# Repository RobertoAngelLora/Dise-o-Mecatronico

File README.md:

# Dise-o-Mecatronico
Materia Electiva de Mecatrónica - Diseño Mecatrónico

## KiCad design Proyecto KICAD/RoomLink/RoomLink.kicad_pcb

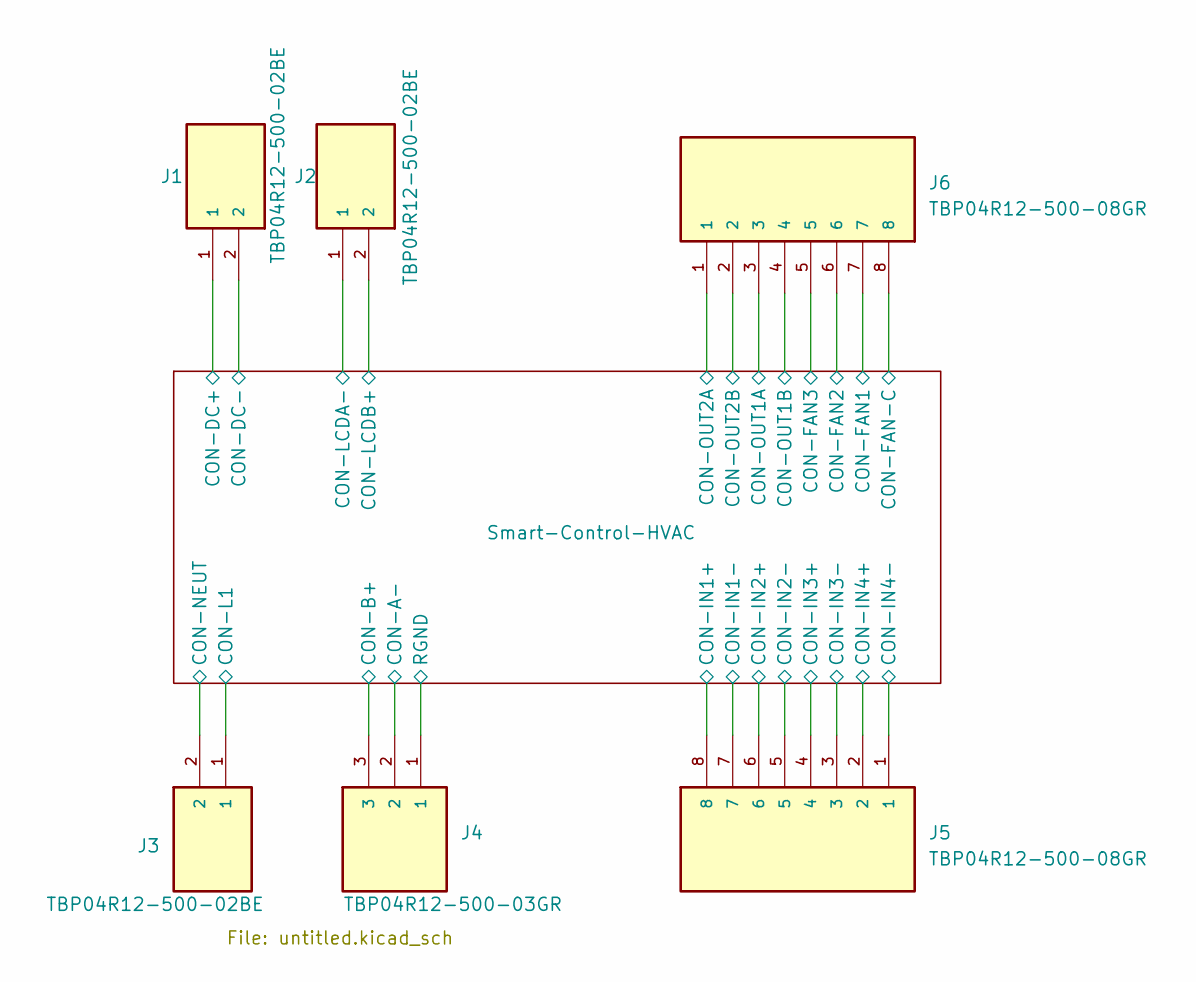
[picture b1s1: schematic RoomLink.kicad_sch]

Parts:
J1, J2, J3: TBP04R12-500-02BE; CUI_TBP04R12-500-02BE; PARTREV 1.0
J4: TBP04R12-500-03GR; CUI_TBP04R12-500-03GR; PARTREV 1.0
J5, J6: TBP04R12-500-08GR; CUI_TBP04R12-500-08GR; PARTREV 1.0

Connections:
/Smart-Control-HVAC/CON-A-: J4.2; also elsewhere on the board
/Smart-Control-HVAC/CON-B+: J4.3; also elsewhere on the board
/Smart-Control-HVAC/CON-DC+: J1.1; also elsewhere on the board
/Smart-Control-HVAC/CON-DC-: J1.2; also elsewhere on the board
/Smart-Control-HVAC/CON-FAN1: J6.7; also elsewhere on the board
/Smart-Control-HVAC/CON-FAN2: J6.6; also elsewhere on the board
/Smart-Control-HVAC/CON-FAN3: J6.5; also elsewhere on the board
/Smart-Control-HVAC/CON-FAN-C: J6.8; also elsewhere on the board
/Smart-Control-HVAC/CON-IN1+: J5.8; also elsewhere on the board
/Smart-Control-HVAC/CON-IN1-: J5.7; also elsewhere on the board
/Smart-Control-HVAC/CON-IN2+: J5.6; also elsewhere on the board
/Smart-Control-HVAC/CON-IN2-: J5.5; also elsewhere on the board
/Smart-Control-HVAC/CON-IN3+: J5.4; also elsewhere on the board
/Smart-Control-HVAC/CON-IN3-: J5.3; also elsewhere on the board
/Smart-Control-HVAC/CON-IN4+: J5.2; also elsewhere on the board
/Smart-Control-HVAC/CON-IN4-: J5.1; also elsewhere on the board
/Smart-Control-HVAC/CON-L1: J2.1; also elsewhere on the board
/Smart-Control-HVAC/CON-LCDA-: J3.1; also elsewhere on the board
/Smart-Control-HVAC/CON-LCDB+: J3.2; also elsewhere on the board
/Smart-Control-HVAC/CON-NEUT: J2.2; also elsewhere on the board
/Smart-Control-HVAC/CON-OUT1A: J6.3; also elsewhere on the board
/Smart-Control-HVAC/CON-OUT1B: J6.4; also elsewhere on the board
/Smart-Control-HVAC/CON-OUT2A: J6.1; also elsewhere on the board
/Smart-Control-HVAC/CON-OUT2B: J6.2; also elsewhere on the board
/Smart-Control-HVAC/RGND: J4.1; also elsewhere on the board

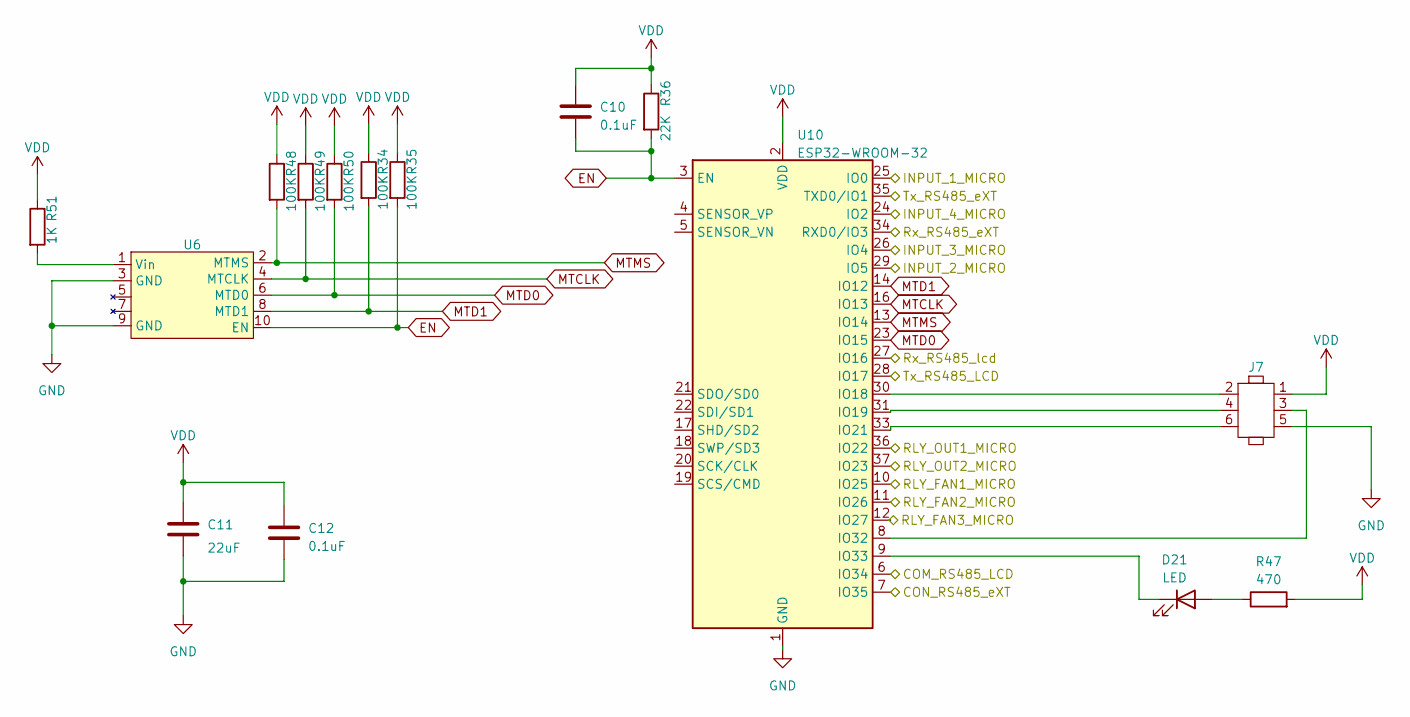
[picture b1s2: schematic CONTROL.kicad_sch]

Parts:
C10, C12: 0.1uF; C_0805_2012Metric
C11: 22uF; C_0805_2012Metric
D21: LED; D_0805_2012Metric
J7: PinHeader_2x03_P2.54mm_Vertical
R34, R35, R48, R49, R50: 100K; R_0805_2012Metric
R36: 22K; R_0805_2012Metric
R47: 470; R_0805_2012Metric
R51: 1K; R_0805_2012Metric
U6: PinHeader_2x05_P2.54mm_Vertical
U10: ESP32-WROOM-32

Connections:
/Smart-Control-HVAC/CONTROL/COM_RS485_LCD: U10.6 (IO34); also elsewhere on the board
/Smart-Control-HVAC/CONTROL/CON_RS485_eXT: U10.7 (IO35); also elsewhere on the board
/Smart-Control-HVAC/CONTROL/INPUT_1_MICRO: U10.25 (IO0); also elsewhere on the board
/Smart-Control-HVAC/CONTROL/INPUT_2_MICRO: U10.29 (IO5); also elsewhere on the board
/Smart-Control-HVAC/CONTROL/INPUT_3_MICRO: U10.26 (IO4); also elsewhere on the board
/Smart-Control-HVAC/CONTROL/INPUT_4_MICRO: U10.24 (IO2); also elsewhere on the board
/Smart-Control-HVAC/CONTROL/RLY_FAN1_MICRO: U10.10 (IO25); also elsewhere on the board
/Smart-Control-HVAC/CONTROL/RLY_FAN2_MICRO: U10.11 (IO26); also elsewhere on the board
/Smart-Control-HVAC/CONTROL/RLY_FAN3_MICRO: U10.12 (IO27); also elsewhere on the board
/Smart-Control-HVAC/CONTROL/RLY_OUT1_MICRO: U10.36 (IO22); also elsewhere on the board
/Smart-Control-HVAC/CONTROL/RLY_OUT2_MICRO: U10.37 (IO23); also elsewhere on the board
/Smart-Control-HVAC/CONTROL/Rx_RS485_eXT: U10.34 (RXD0/IO3); also elsewhere on the board
/Smart-Control-HVAC/CONTROL/Rx_RS485_lcd: U10.27 (IO16); also elsewhere on the board
/Smart-Control-HVAC/CONTROL/Tx_RS485_LCD: U10.28 (IO17); also elsewhere on the board
/Smart-Control-HVAC/CONTROL/Tx_RS485_eXT: U10.35 (TXD0/IO1); also elsewhere on the board
EN: C10.2, R35.2, R36.2, U6.10 (EN), U10.3 (EN)
GND: C11.2, C12.2, J7.5, U6.3 (GND), U6.9 (GND), U10.1 (GND), U10.15 (GND), U10.38 (GND), U10.39 (GND); also elsewhere on the board
MTCLK: R49.2, U6.4 (MTCLK), U10.16 (IO13)
MTD0: R50.2, U6.6 (MTD0), U10.23 (IO15)
MTD1: R34.2, U6.8 (MTD1), U10.14 (IO12)
MTMS: R48.2, U6.2 (MTMS), U10.13 (IO14)
unnamed: D21.2 (A), R47.1
unnamed: D21.1 (K), U10.9 (IO33)
unnamed: R51.2, U6.1 (Vin)
unnamed: J7.2, U10.30 (IO18)
unnamed: J7.4, U10.31 (IO19)
unnamed: J7.6, U10.33 (IO21)
unnamed: J7.3, U10.8 (IO32)
VDD: C10.1, C11.1, C12.1, J7.1, R34.1, R35.1, R36.1, R47.2, R48.1, R49.1, R50.1, R51.1, U10.2 (VDD); also elsewhere on the board

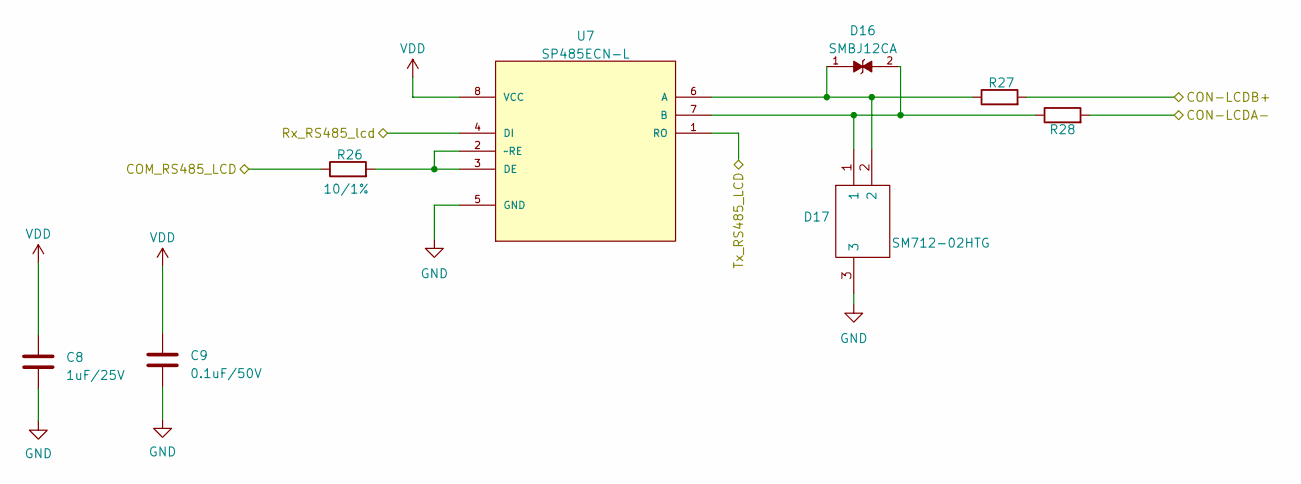
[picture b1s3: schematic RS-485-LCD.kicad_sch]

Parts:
C8: 1uF/25V; C_0805_2012Metric
C9: 0.1uF/50V; C_0805_2012Metric
D16: SMBJ12CA; DIOM4336X265N; PARTREV I2102
D17: SM712-02HTG; SM71202HTG; Mouser Part Number 576-SM712-02HTG
R26, R27, R28: 10/1%; R_0805_2012Metric
U7: SP485ECN-L; SOIC127P600X175-8N; MPN SP485ECN-L

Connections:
/Smart-Control-HVAC/CON-LCDA-: R28.2; also elsewhere on the board
/Smart-Control-HVAC/CON-LCDB+: R27.2; also elsewhere on the board
/Smart-Control-HVAC/CONTROL/COM_RS485_LCD: R26.1; also elsewhere on the board
/Smart-Control-HVAC/CONTROL/Rx_RS485_lcd: U7.4 (DI); also elsewhere on the board
/Smart-Control-HVAC/CONTROL/Tx_RS485_LCD: U7.1 (RO); also elsewhere on the board
GND: C8.2, C9.2, D17.3, U7.5 (GND); also elsewhere on the board
unnamed: D16.1, D17.2, R27.1, U7.6 (A)
unnamed: D16.2, D17.1, R28.1, U7.7 (B)
unnamed: R26.2, U7.2 (~RE), U7.3 (DE)
VDD: C8.1, C9.1, U7.8 (VCC); also elsewhere on the board

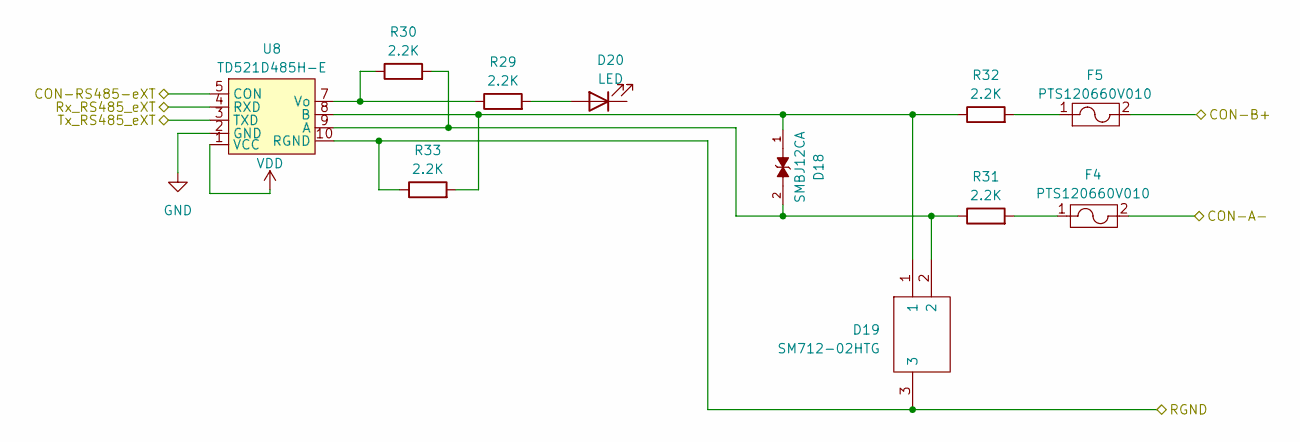
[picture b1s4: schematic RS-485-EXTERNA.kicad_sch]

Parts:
D18: SMBJ12CA; DIOM4336X265N; PARTREV I2102
D19: SM712-02HTG; SM71202HTG; Mouser Part Number 576-SM712-02HTG
D20: LED; LED_0805_2012Metric
F4, F5: PTS120660V010; RESC3115X65N
R29, R30, R31, R32, R33: 2.2K; R_0805_2012Metric
U8: TD521D485H-E

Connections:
/Smart-Control-HVAC/CON-A-: F4.2; also elsewhere on the board
/Smart-Control-HVAC/CON-B+: F5.2; also elsewhere on the board
/Smart-Control-HVAC/CONTROL/CON_RS485_eXT: U8.5 (CON); also elsewhere on the board
/Smart-Control-HVAC/CONTROL/Rx_RS485_eXT: U8.4 (RXD); also elsewhere on the board
/Smart-Control-HVAC/CONTROL/Tx_RS485_eXT: U8.3 (TXD); also elsewhere on the board
/Smart-Control-HVAC/RGND: D19.3, R33.1, U8.10 (RGND); also elsewhere on the board
GND: U8.2 (GND); also elsewhere on the board
unnamed: D20.2 (A), R29.2
unnamed: F4.1, R31.2
unnamed: F5.1, R32.2
unnamed: D18.2, D19.2, R30.2, R31.1, U8.9 (A)
unnamed: D18.1, D19.1, R32.1, R33.2, U8.8 (B)
unnamed: R29.1, R30.1, U8.7 (Vo)
VDD: U8.1 (VCC); also elsewhere on the board

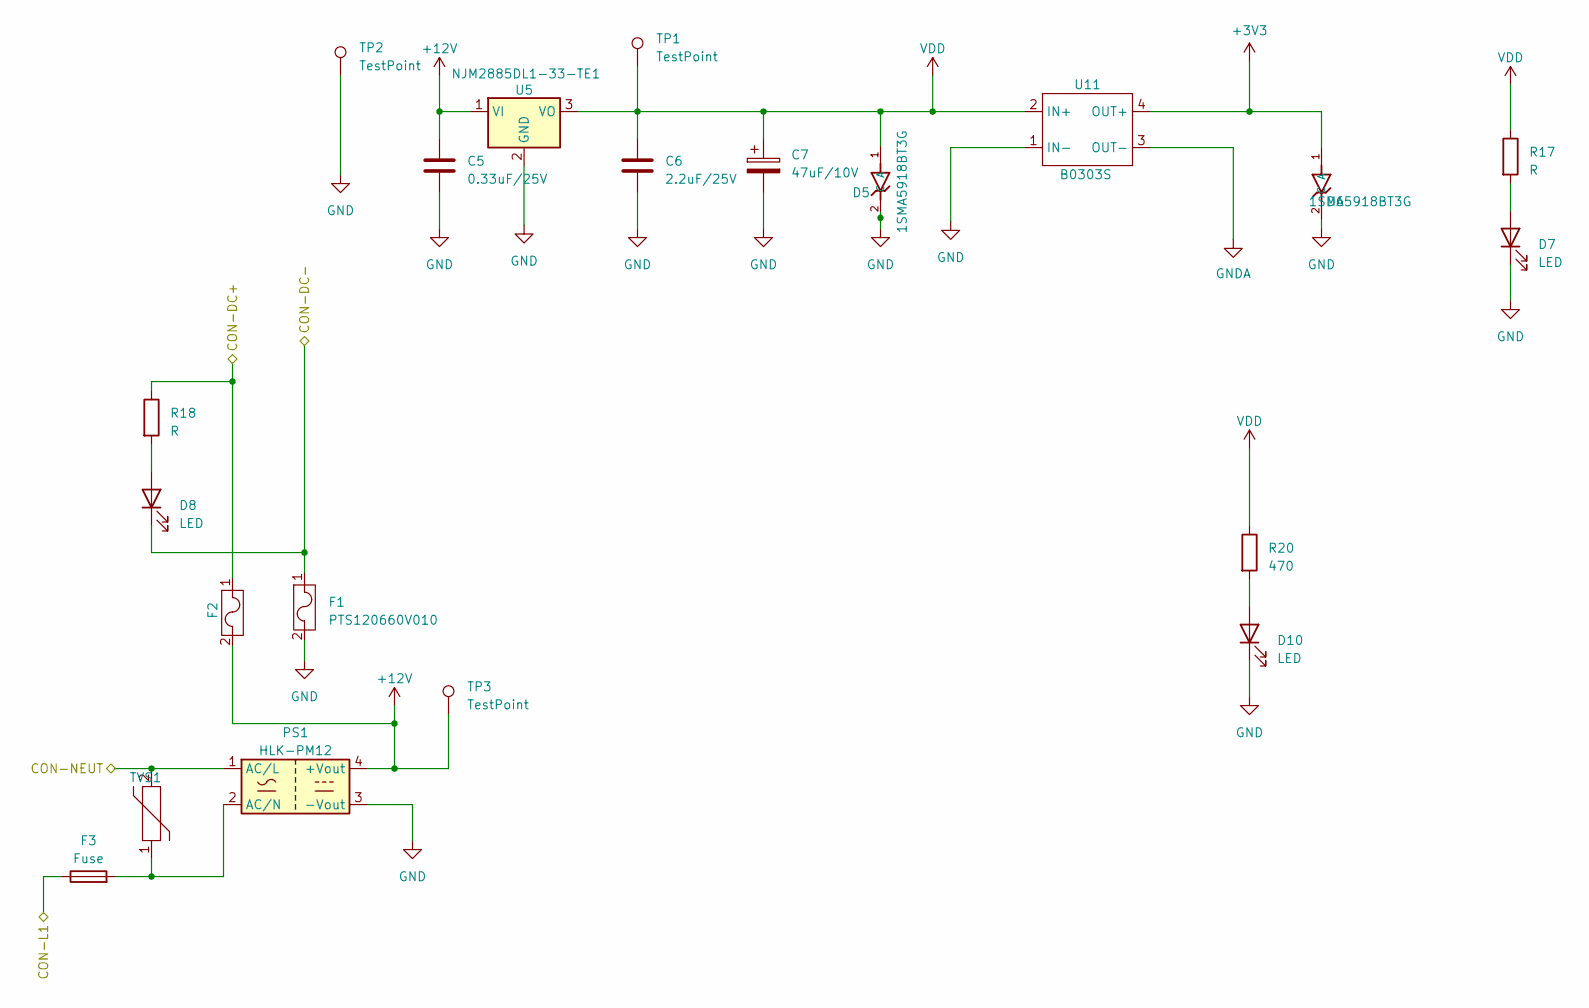
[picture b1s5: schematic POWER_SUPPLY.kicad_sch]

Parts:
C5: 0.33uF/25V; C_0805_2012Metric
C6: 2.2uF/25V; C_0805_2012Metric
C7: 47uF/10V; C_0805_2012Metric
D5, D6: 1SMA5918BT3G; D_0805_2012Metric; PARTREV 10
D7, D8, D10: LED; D_0805_2012Metric
F1, F2: PTS120660V010; Fuse_1206_3216Metric
F3: Fuse; Fuseholder_Cylinder-5x20mm_Stelvio-Kontek_PTF78_Horizontal_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
PS1: HLK-PM12; Converter_ACDC_HiLink_HLK-PMxx
R17, R18: R; D_0805_2012Metric
R20: 470; D_0805_2012Metric
TP1, TP2, TP3: TestPoint; TestPoint_Loop_D1.80mm_Drill1.0mm_Beaded
TVS1: RV_Disc_D21.5mm_W7.5mm_P10mm
U5: NJM2885DL1-33-TE1; DPAK228P968X238-4N
U11: B0303S; B0505S-W2R2

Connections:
+3V3: D6.1 (A), U11.4 (OUT+); also elsewhere on the board
+12V: C5.1, F2.2, PS1.4 (+Vout), TP3.1, U5.1 (VI); also elsewhere on the board
/Smart-Control-HVAC/CON-DC+: F2.1, R18.1; also elsewhere on the board
/Smart-Control-HVAC/CON-DC-: D8.1 (K), F1.1; also elsewhere on the board
/Smart-Control-HVAC/CON-L1: F3.1; also elsewhere on the board
/Smart-Control-HVAC/CON-NEUT: PS1.1 (AC/L), TVS1.2; also elsewhere on the board
GND: C5.2, C6.2, C7.2, D5.2 (C), D6.2 (C), D7.1 (K), D10.1 (K), F1.2, PS1.3 (-Vout), TP2.1, U5.2 (GND), U11.1 (IN-); also elsewhere on the board
GNDA: U11.3 (OUT-); also elsewhere on the board
unnamed: D7.2 (A), R17.2
unnamed: D8.2 (A), R18.2
unnamed: D10.2 (A), R20.2
unnamed: F3.2, PS1.2 (AC/N), TVS1.1
VDD: C6.1, C7.1, D5.1 (A), R17.1, R20.1, TP1.1, U5.3 (VO), U11.2 (IN+); also elsewhere on the board

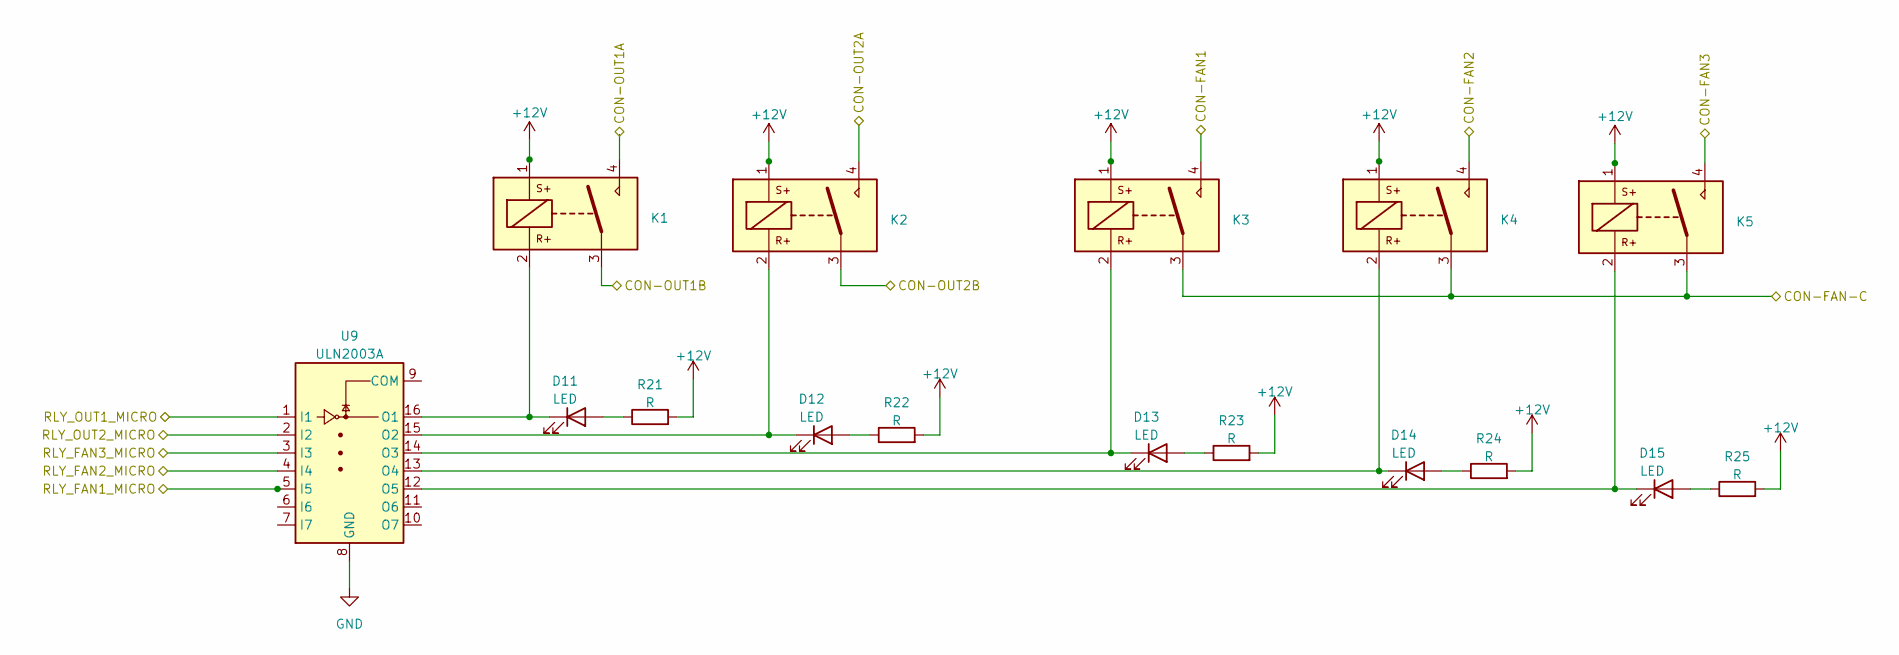
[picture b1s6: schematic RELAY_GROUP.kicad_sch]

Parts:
D11, D12, D13, D14, D15: LED; LED_0805_2012Metric
K1, K2, K3, K4, K5: AZ921
R21, R22, R23, R24, R25: R; R_0805_2012Metric
U9: ULN2003A; SOIC-16_3.9x9.9mm_P1.27mm

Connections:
+12V: K1.1, K2.1, K3.1, K4.1, K5.1, R21.2, R22.2, R23.2, R24.2, R25.2; also elsewhere on the board
/Smart-Control-HVAC/CON-FAN1: K3.4; also elsewhere on the board
/Smart-Control-HVAC/CON-FAN2: K4.4; also elsewhere on the board
/Smart-Control-HVAC/CON-FAN3: K5.4; also elsewhere on the board
/Smart-Control-HVAC/CON-FAN-C: K3.3, K4.3, K5.3; also elsewhere on the board
/Smart-Control-HVAC/CON-OUT1A: K1.4; also elsewhere on the board
/Smart-Control-HVAC/CON-OUT1B: K1.3; also elsewhere on the board
/Smart-Control-HVAC/CON-OUT2A: K2.4; also elsewhere on the board
/Smart-Control-HVAC/CON-OUT2B: K2.3; also elsewhere on the board
/Smart-Control-HVAC/CONTROL/RLY_FAN1_MICRO: U9.5 (I5); also elsewhere on the board
/Smart-Control-HVAC/CONTROL/RLY_FAN2_MICRO: U9.4 (I4); also elsewhere on the board
/Smart-Control-HVAC/CONTROL/RLY_FAN3_MICRO: U9.3 (I3); also elsewhere on the board
/Smart-Control-HVAC/CONTROL/RLY_OUT1_MICRO: U9.1 (I1); also elsewhere on the board
/Smart-Control-HVAC/CONTROL/RLY_OUT2_MICRO: U9.2 (I2); also elsewhere on the board
GND: U9.8 (GND); also elsewhere on the board
unnamed: D11.2 (A), R21.1
unnamed: D11.1 (K), K1.2, U9.16 (O1)
unnamed: D12.2 (A), R22.1
unnamed: D12.1 (K), K2.2, U9.15 (O2)
unnamed: D13.2 (A), R23.1
unnamed: D13.1 (K), K3.2, U9.14 (O3)
unnamed: D14.2 (A), R24.1
unnamed: D14.1 (K), K4.2, U9.13 (O4)
unnamed: D15.2 (A), R25.1
unnamed: D15.1 (K), K5.2, U9.12 (O5)

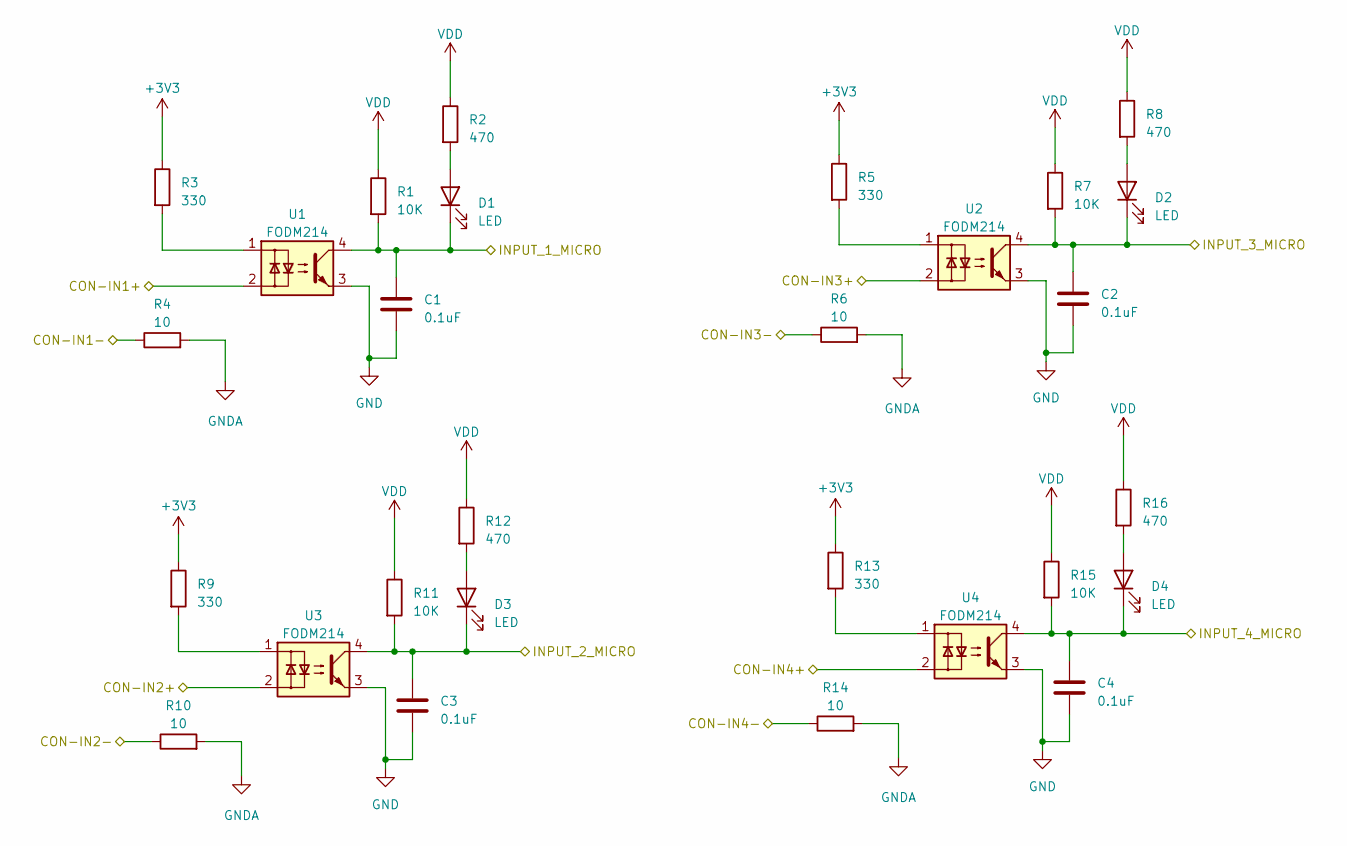
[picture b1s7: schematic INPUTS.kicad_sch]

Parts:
C1, C2, C3, C4: 0.1uF; C_0805_2012Metric
D1, D2, D3, D4: LED; LED_0805_2012Metric
R1, R7, R11, R15: 10K; R_0805_2012Metric
R2, R8, R12, R16: 470; R_0805_2012Metric
R3, R5, R9, R13: 330; R_0805_2012Metric
R4, R6, R10, R14: 10; R_0805_2012Metric
U1, U2, U3, U4: FODM214; SOP-4_4.4x2.6mm_P1.27mm

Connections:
+3V3: R3.1, R5.1, R9.1, R13.1; also elsewhere on the board
/Smart-Control-HVAC/CON-IN1+: U1.2; also elsewhere on the board
/Smart-Control-HVAC/CON-IN1-: R4.1; also elsewhere on the board
/Smart-Control-HVAC/CON-IN2+: U3.2; also elsewhere on the board
/Smart-Control-HVAC/CON-IN2-: R10.1; also elsewhere on the board
/Smart-Control-HVAC/CON-IN3+: U2.2; also elsewhere on the board
/Smart-Control-HVAC/CON-IN3-: R6.1; also elsewhere on the board
/Smart-Control-HVAC/CON-IN4+: U4.2; also elsewhere on the board
/Smart-Control-HVAC/CON-IN4-: R14.1; also elsewhere on the board
/Smart-Control-HVAC/CONTROL/INPUT_1_MICRO: C1.1, D1.1 (K), R1.2, U1.4; also elsewhere on the board
/Smart-Control-HVAC/CONTROL/INPUT_2_MICRO: C3.1, D3.1 (K), R11.2, U3.4; also elsewhere on the board
/Smart-Control-HVAC/CONTROL/INPUT_3_MICRO: C2.1, D2.1 (K), R7.2, U2.4; also elsewhere on the board
/Smart-Control-HVAC/CONTROL/INPUT_4_MICRO: C4.1, D4.1 (K), R15.2, U4.4; also elsewhere on the board
GND: C1.2, C2.2, C3.2, C4.2, U1.3, U2.3, U3.3, U4.3; also elsewhere on the board
GNDA: R4.2, R6.2, R10.2, R14.2; also elsewhere on the board
unnamed: D1.2 (A), R2.2
unnamed: D2.2 (A), R8.2
unnamed: D3.2 (A), R12.2
unnamed: D4.2 (A), R16.2
unnamed: R3.2, U1.1
unnamed: R5.2, U2.1
unnamed: R9.2, U3.1
unnamed: R13.2, U4.1
VDD: R1.1, R2.1, R7.1, R8.1, R11.1, R12.1, R15.1, R16.1; also elsewhere on the board

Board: 4 copper layers, 105 parts (0 on the bottom side), 88 nets, no tracks yet.

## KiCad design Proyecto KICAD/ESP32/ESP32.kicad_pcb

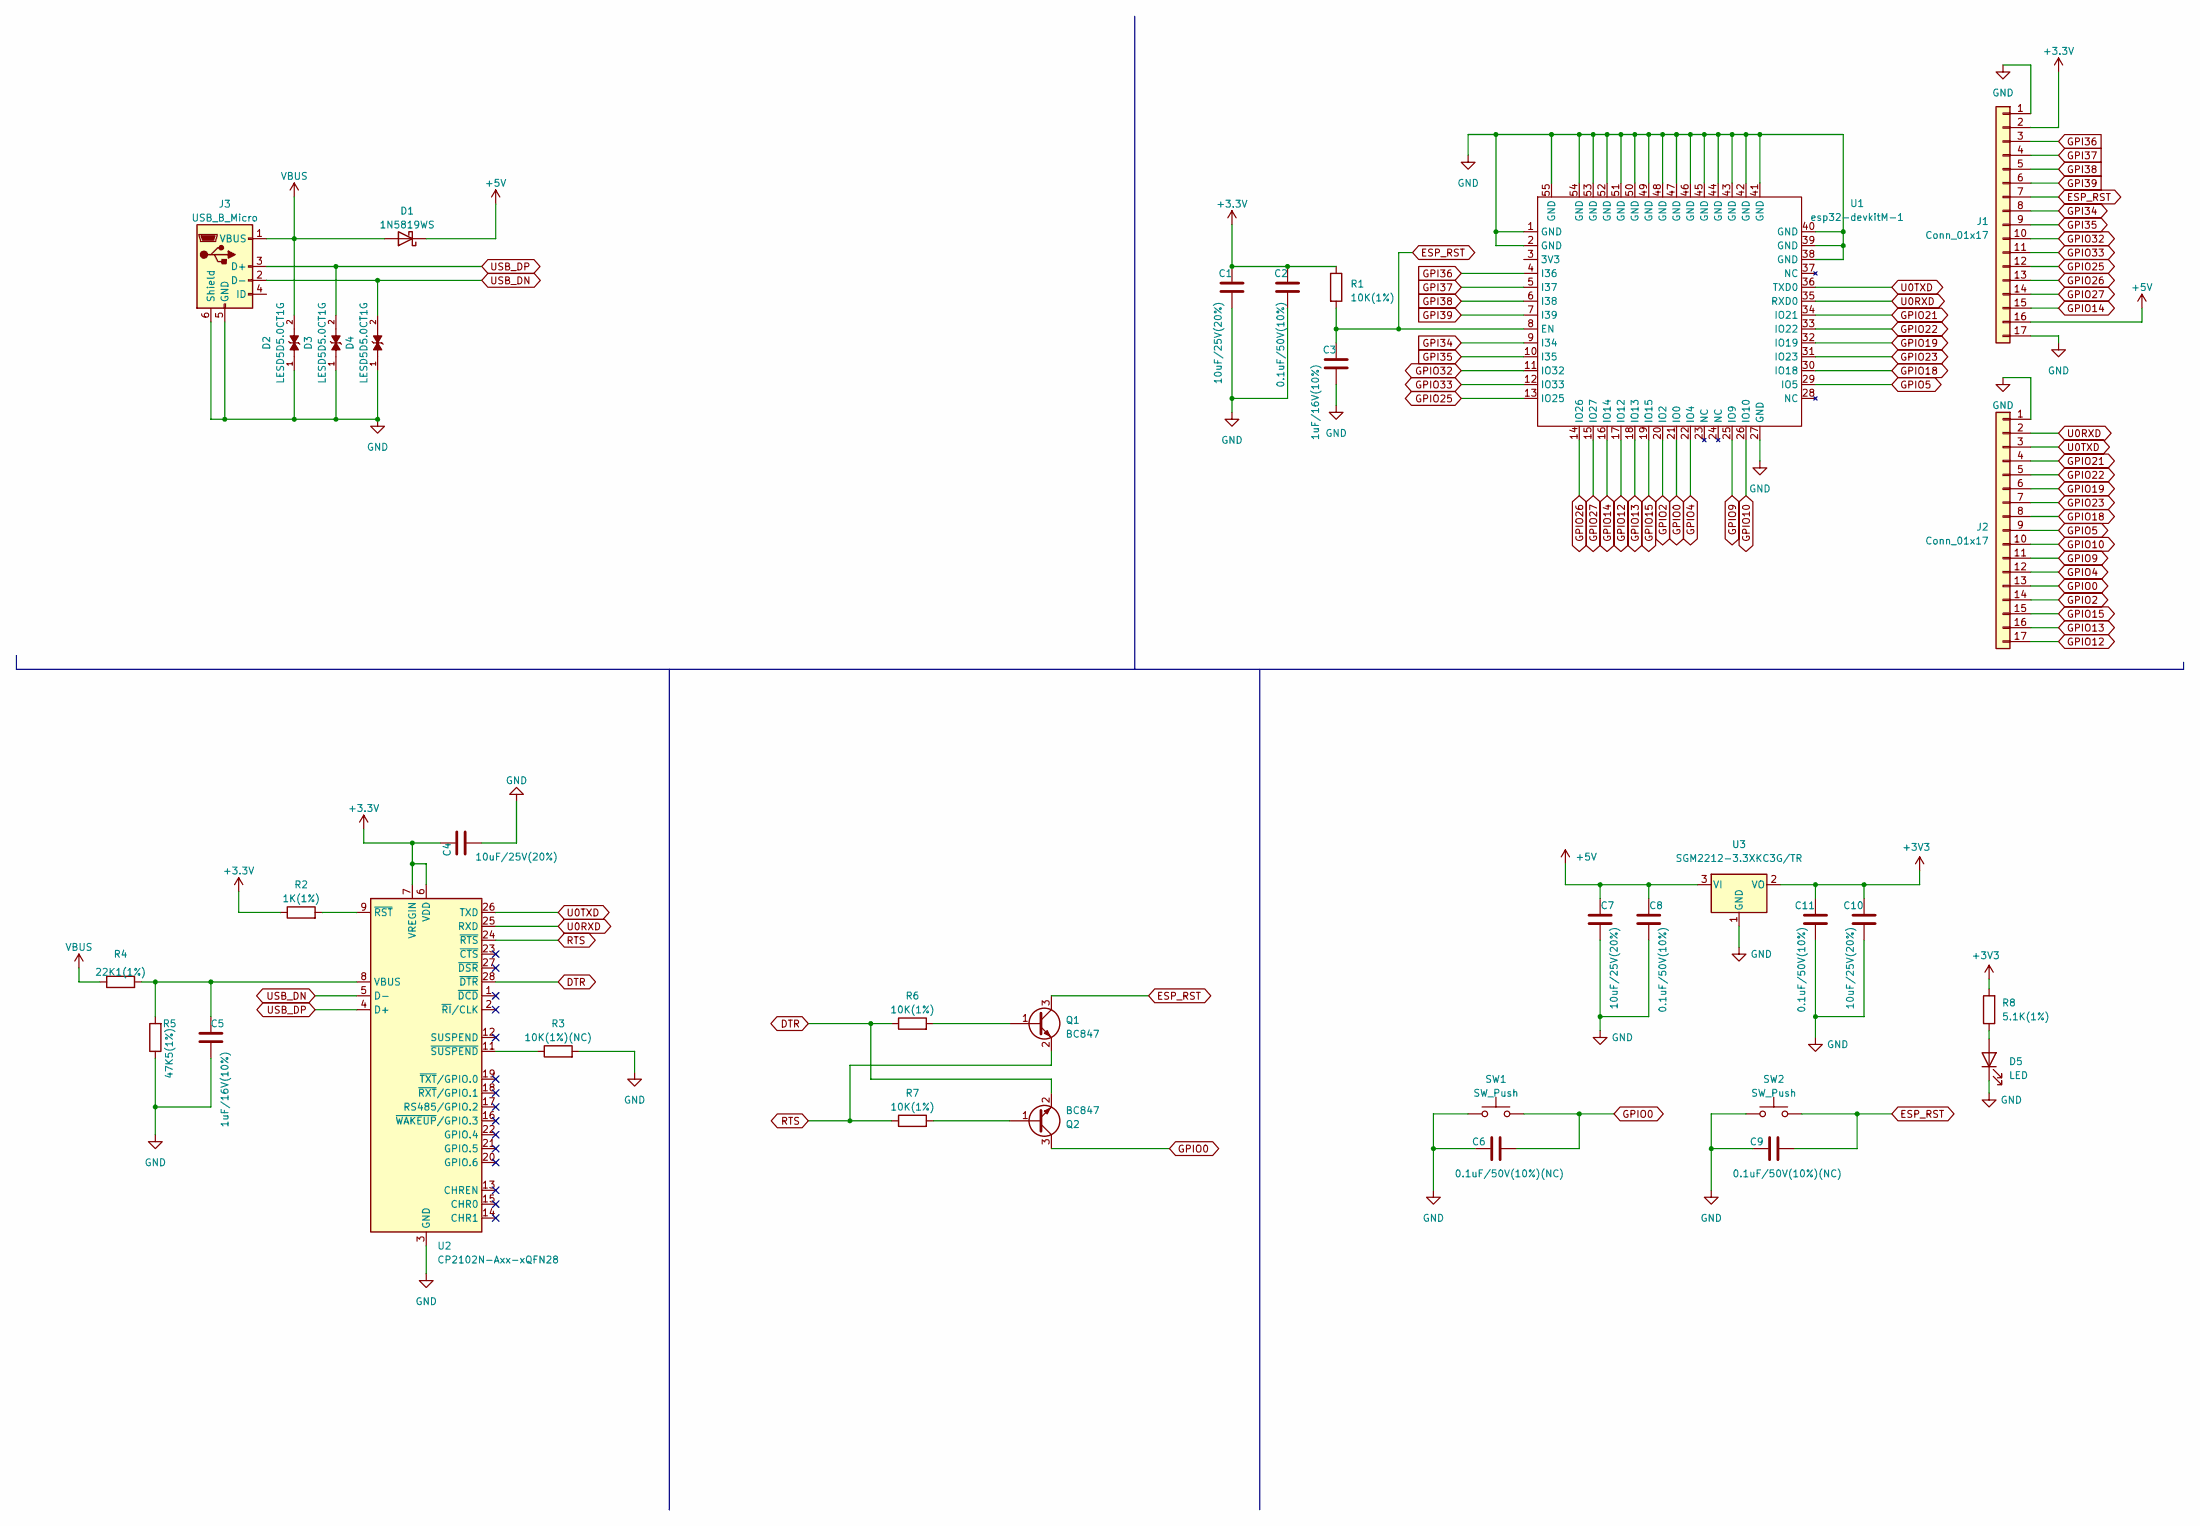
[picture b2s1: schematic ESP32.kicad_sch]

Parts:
C1, C4, C7, C10: 10uF/25V(20%); C_0805_2012Metric
C2, C8, C11: 0.1uF/50V(10%); C_0805_2012Metric
C3, C5: 1uF/16V(10%); C_0805_2012Metric
C6, C9: 0.1uF/50V(10%)(NC); C_0805_2012Metric
D1: 1N5819WS; D_SOD-323
D2, D3, D4: LESD5D5.0CT1G; TVS_LESD5D5.0CT1G; PARTREV O
D5: LED; LED_0805_2012Metric
J1, J2: Conn_01x17; PinHeader_1x17_P2.54mm_Vertical
J3: USB_B_Micro; USB_Micro-B_Wuerth_629105150521
Q1, Q2: BC847; SOT-23
R1, R6, R7: 10K(1%); R_0805_2012Metric
R2: 1K(1%); R_0805_2012Metric
R3: 10K(1%)(NC); R_0805_2012Metric
R4: 22K1(1%); R_0805_2012Metric
R5: 47K5(1%); R_0805_2012Metric
R8: 5.1K(1%); R_0805_2012Metric
SW1, SW2: SW_Push; SW_SPST_PTS810
U1: esp32-devkitM-1
U2: CP2102N-Axx-xQFN28; QFN-28-1EP_5x5mm_P0.5mm_EP3.35x3.35mm
U3: SGM2212-3.3XKC3G/TR; SOT-23

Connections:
+5V: C7.1, C8.1, D1.1 (K), J1.16, U3.3 (VI)
DTR: Q2.2 (E), R6.1, U2.28 (~DTR)
ESP_RST: C3.1, C9.2, J1.7, Q1.3 (C), R1.2, SW2.2, U1.8 (EN)
GND: C1.2, C2.2, C3.2, C4.2, C5.1, C6.1, C7.2, C8.2, C9.1, C10.2, C11.2, D2.1, D3.1, D4.1, D5.1 (K), J1.1, J1.17, J2.1, J3.5 (GND), J3.6 (Shield), R3.2, R5.1, SW1.1, SW2.1, U1.1 (GND), U1.2 (GND), U1.27 (GND), U1.38 (GND), U1.39 (GND), U1.40 (GND), U1.41 (GND), U1.42 (GND), U1.43 (GND), U1.44 (GND), U1.45 (GND), U1.46 (GND), U1.47 (GND), U1.48 (GND), U1.49 (GND), U1.50 (GND), U1.51 (GND), U1.52 (GND), U1.53 (GND), U1.54 (GND), U1.55 (GND), U2.3 (GND), U2.29 (GND), U3.1 (GND)
GPI34: J1.8, U1.9 (I34)
GPI35: J1.9, U1.10 (I35)
GPI36: J1.3, U1.4 (I36)
GPI37: J1.4, U1.5 (I37)
GPI38: J1.5, U1.6 (I38)
GPI39: J1.6, U1.7 (I39)
GPIO0: C6.2, J2.13, Q2.3 (C), SW1.2, U1.21 (IO0)
GPIO2: J2.14, U1.20 (IO2)
GPIO4: J2.12, U1.22 (IO4)
GPIO5: J2.9, U1.29 (IO5)
GPIO9: J2.11, U1.25 (IO9)
GPIO10: J2.10, U1.26 (IO10)
GPIO12: J2.17, U1.17 (IO12)
GPIO13: J2.16, U1.18 (IO13)
GPIO14: J1.15, U1.16 (IO14)
GPIO15: J2.15, U1.19 (IO15)
GPIO18: J2.8, U1.30 (IO18)
GPIO19: J2.6, U1.32 (IO19)
GPIO21: J2.4, U1.34 (IO21)
GPIO22: J2.5, U1.33 (IO22)
GPIO23: J2.7, U1.31 (IO23)
GPIO25: J1.12, U1.13 (IO25)
GPIO26: J1.13, U1.14 (IO26)
GPIO27: J1.14, U1.15 (IO27)
GPIO32: J1.10, U1.11 (IO32)
GPIO33: J1.11, U1.12 (IO33)
unnamed: D5.2 (A), R8.1
unnamed: Q1.1 (B), R6.2
unnamed: Q2.1 (B), R7.2
unnamed: C5.2, R4.2, R5.2, U2.8 (VBUS)
unnamed: R2.2, U2.9 (~RST)
unnamed: R3.1, U2.11 (~SUSPEND)
RTS: Q1.2 (E), R7.1, U2.24 (~RTS)
U0RXD: J2.2, U1.35 (RXD0), U2.25 (RXD)
U0TXD: J2.3, U1.36 (TXD0), U2.26 (TXD)
USB_DN: D4.2, J3.2 (D-), U2.5 (D-)
USB_DP: D3.2, J3.3 (D+), U2.4 (D+)
VBUS: D1.2 (A), D2.2, J3.1 (VBUS), R4.1

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
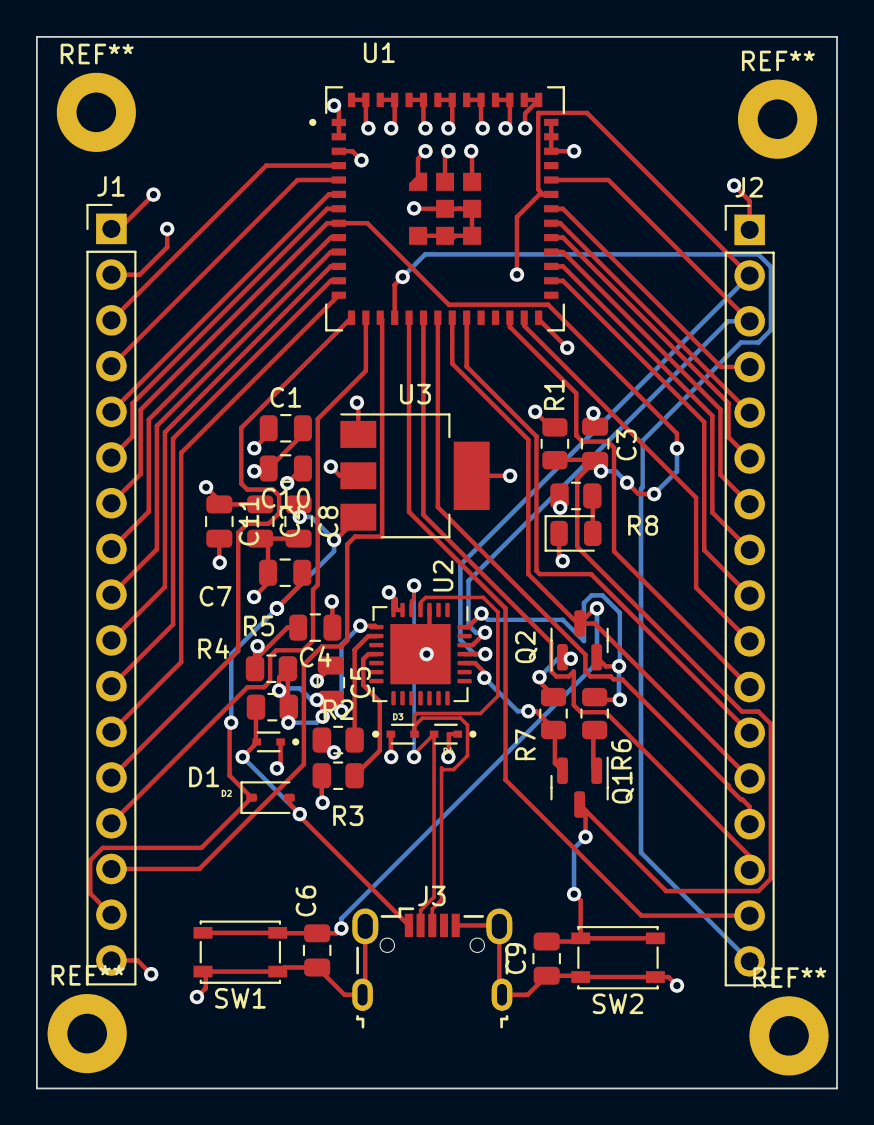
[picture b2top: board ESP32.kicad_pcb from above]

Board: 4 copper layers, 44.4 x 58.4 mm, 34 parts (0 on the bottom side), 43 nets.

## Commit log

2023-05-26 Anotaciones
2023-06-09 Proyecto Kicad
2023-06-20 Esquematico
2023-06-25 Room Link
2023-06-26 Room link1
2023-06-27 BLLLLLL
2023-08-18 Raymundo
2023-09-18 Create RoomLink
2023-09-18 Todo
